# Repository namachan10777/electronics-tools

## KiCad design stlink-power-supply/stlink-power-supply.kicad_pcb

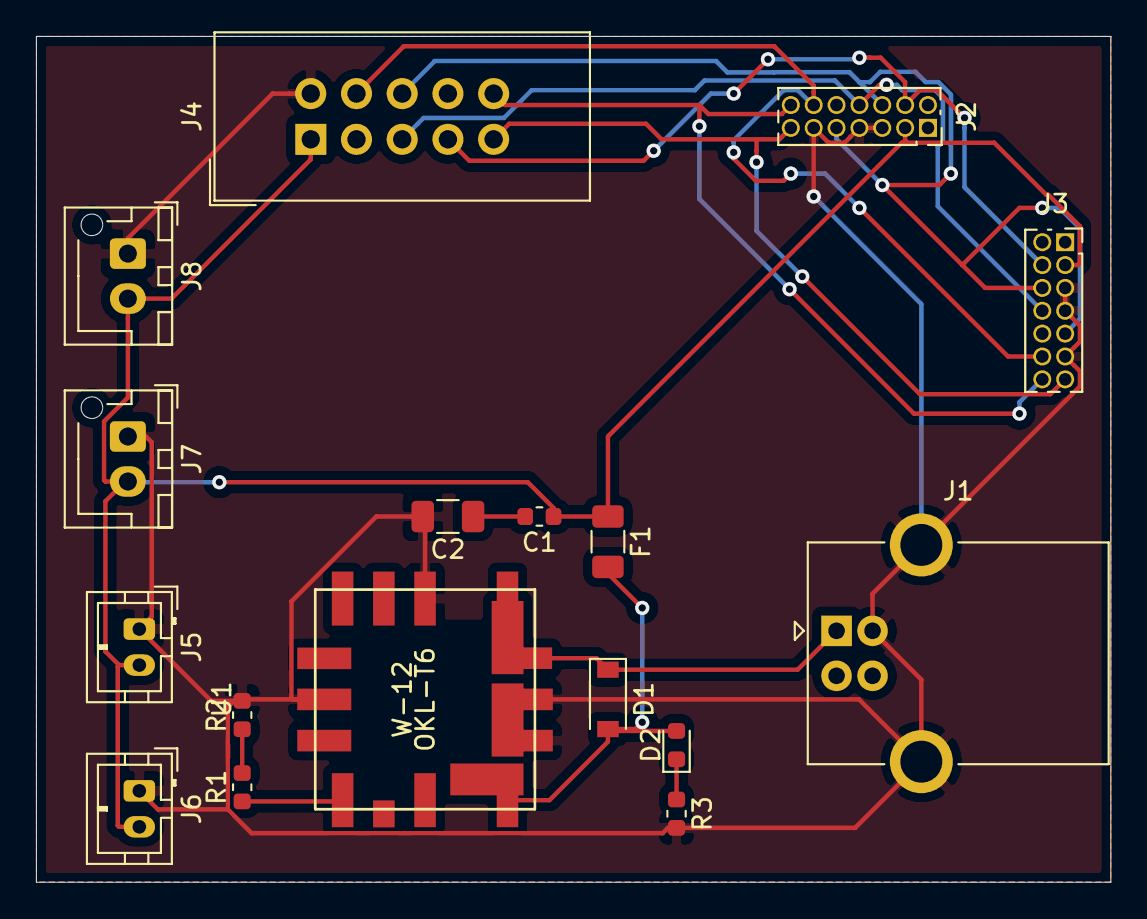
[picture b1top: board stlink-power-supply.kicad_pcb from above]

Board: 2 copper layers, 59.7 x 47.0 mm, 17 parts (0 on the bottom side), 14 nets.

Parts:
C1: 0.1uF; C_0603_1608Metric
C2: 10uF; C_1206_3216Metric
D1: RevD; D_SOD-123
D2: D; LED_0603_1608Metric
F1: Polyfuse; Fuse_1206_3216Metric
J1: USB_B; USB_B_OST_USB-B1HSxx_Horizontal
J2, J3: STLinkV3-MINI; PinSocket_2x07_P1.27mm_Vertical
J4: DEBUG; IDC-Header_2x05_P2.54mm_Vertical
J5, J6: out; JST_PH_B2B-PH-K_1x02_P2.00mm_Vertical
J7, J8: out; JST_XH_B2B-XH-AM_1x02_P2.50mm_Vertical
R1: 1.5kΩ; R_0603_1608Metric
R2: 680Ω; R_0603_1608Metric
R3: 220Ω; R_0603_1608Metric
U1: OKL-T6-W12

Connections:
+3V3: C1.1, F1.1, J2.3, J3.3, J4.1, J5.2, J6.2, J7.2, J8.2
+5V: D1.1, J1.1, U1.A1
/RST: J2.12, J3.12, J4.4
/RX: J2.13, J3.13, J4.9
/SWCLK: J2.6, J2.9, J3.6, J3.9, J4.6
/SWDIO: J2.4, J3.4, J4.7
/SWO: J2.8, J3.8, J4.5
/TX: J2.14, J3.14, J4.10
GND: C2.2, J1.4, J1.5, J2.5, J2.7, J2.11, J3.5, J3.7, J3.11, J4.2, J5.1, J6.1, J7.1, J8.1, R2.2, R3.2, U1.A3, U1.C1
unnamed: C1.2, C2.1
unnamed: D1.2, D2.2, F1.2, U1.A5
unnamed: D2.1, R3.1
unnamed: R1.1, U1.E5
unnamed: R1.2, R2.1

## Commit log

2020-01-19 STLink power supplier
2020-01-19 add another interface
